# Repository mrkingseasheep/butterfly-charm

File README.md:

# Butterfly Charm

This is a very simple butterfly charm which is basically a light up trinket that you can hopefully attach to your bag.
It features large vias for keychains.
The LEDs only turn on when it is dark outside, preserving battery power and becoming more eye-catching in the dark.
The circuit uses a photoresistor in tandem with a transistor to determine whether or not it is light outside.
When there is light, the photoresistor decreases in resistence, therefore lowering electron flow to the base gate of the transistor, preventing the 2 LEDs from getting enough current to significantly light up.
When there is no light, the resistence in the photoresistor increases, therefore more current flows through the base gate (around 0.05miliamps) allowing 5 miliamps to run the LEDs.
Red LEDs were used because they need the least current.

Slack username: Xinyang Wang

## BOM

| Item                | Qnt |
| ------------------- | --- |
| LEDs                | 2   |
| Battery holder 3034 | 1   |
| Photoresistor       | 1   |
| 220ohm resistors    | 2   |
| 100kOhm resistors   | 1   |
| NPN transistor      | 1   |
| PCB                 | 1   |

## Images

## Thoughts

This was my first time designing a board using Kicad so it's a bit rough around the edges.
Getting the bezier curves to work was especially annoying and it took several iterations to smooth out the lumps.
There's probably a way to make an SVG the (Edges.Cuts) layer instead of having to polyline/curve it out but I'm too lazy to find out how.
The electronics are really simple. It's just connecting togther a battery, a LED, a resistor and a button.
Not much to explain. In fact, the most challenging part was designing the butterfly shape in Krita and getting the pattern on the back to work.
Oh hopefully the comically large vias won't destroy the structural stability of the part because I actually plan on using this.
If I have any advice for other people, it's to not use Kicad with a tiling window manager. It made things really difficult.
Also I almost forgot to run the checker. I just realized that my button holes weren't actually connected to the copper trace beneath them.
Hopefully nothing else is broken...

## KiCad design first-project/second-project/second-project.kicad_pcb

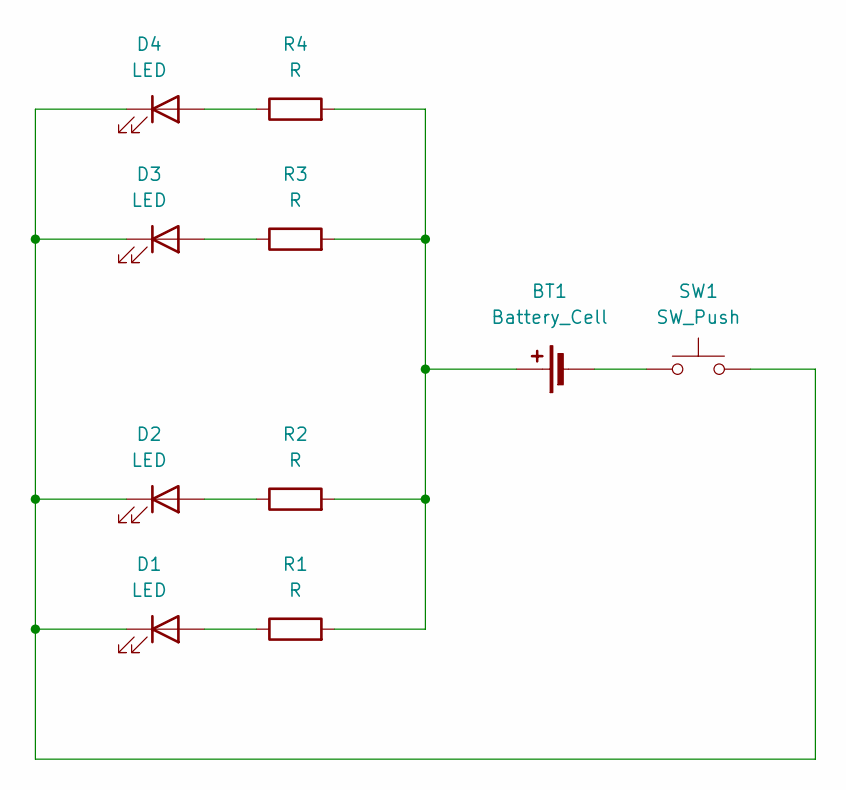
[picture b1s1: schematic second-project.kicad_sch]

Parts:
BT1: Battery_Cell; BatteryHolder_Keystone_3034_1x20mm
D1, D2, D3, D4: LED; LED_D5.0mm
R1, R2, R3, R4: R; R_Axial_DIN0207_L6.3mm_D2.5mm_P7.62mm_Horizontal
SW1: SW_Push; SW_PUSH_6mm

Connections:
unnamed: BT1.1 (+), R1.2, R2.2, R3.2, R4.2
unnamed: BT1.2 (-), SW1.1
unnamed: D1.2 (A), R1.1
unnamed: D1.1 (K), D2.1 (K), D3.1 (K), D4.1 (K), SW1.2
unnamed: D2.2 (A), R2.1
unnamed: D3.2 (A), R3.1
unnamed: D4.2 (A), R4.1

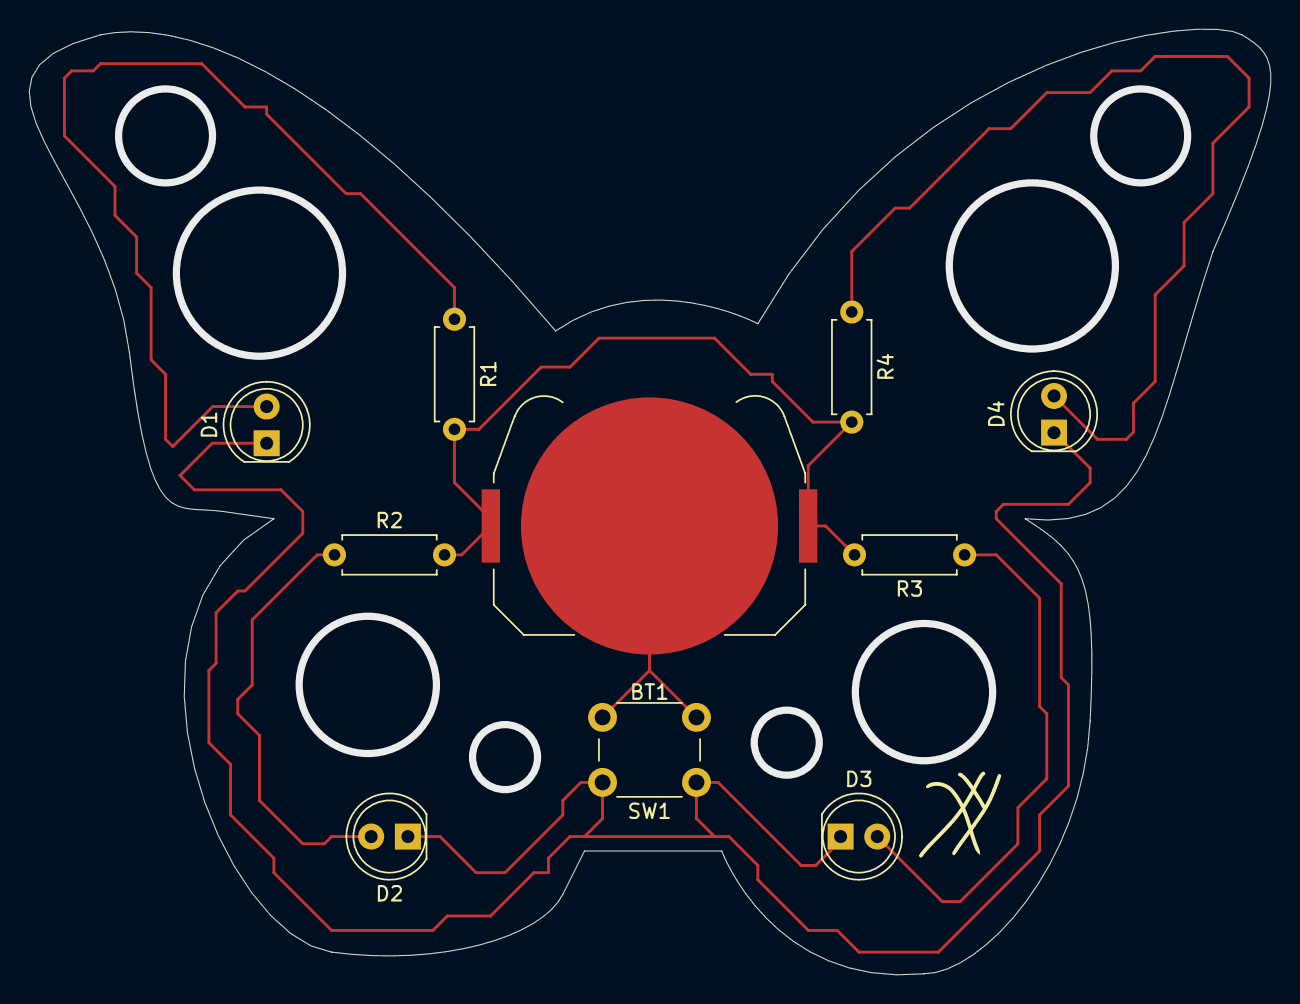
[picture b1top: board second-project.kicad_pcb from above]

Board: 2 copper layers, 85.9 x 65.5 mm, 10 parts (0 on the bottom side), 7 nets.

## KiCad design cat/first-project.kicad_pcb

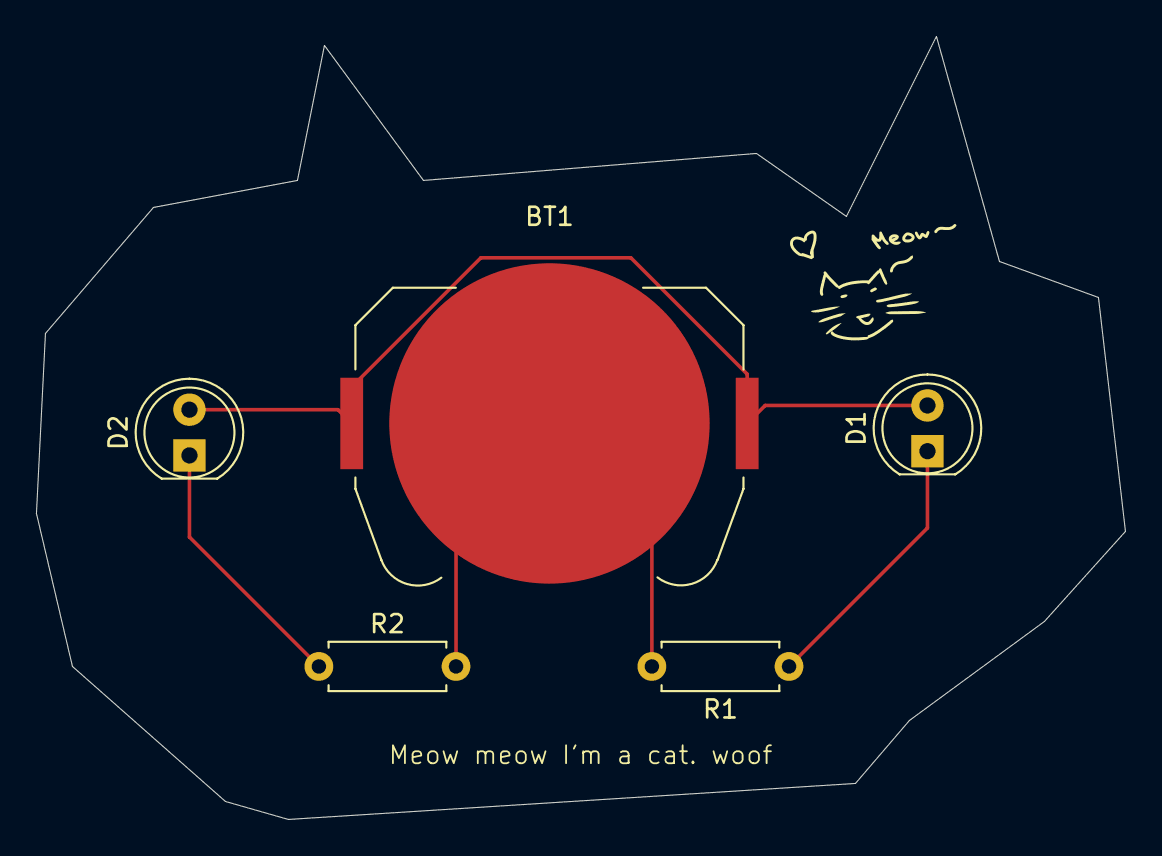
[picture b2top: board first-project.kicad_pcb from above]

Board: 2 copper layers, 60.5 x 43.5 mm, 5 parts (0 on the bottom side), 4 nets.

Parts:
BT1: Battery_Cell; BatteryHolder_Keystone_3034_1x20mm
D1, D2: LED; LED_D5.0mm
R1, R2: R; R_Axial_DIN0207_L6.3mm_D2.5mm_P7.62mm_Horizontal

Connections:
unnamed: BT1.1 (+), D1.2 (A), D2.2 (A)
unnamed: BT1.2 (-), R1.2, R2.2
unnamed: D1.1 (K), R1.1
unnamed: D2.1 (K), R2.1

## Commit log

2025-06-17 First cat
2025-06-18 second iteration
2025-06-18 added readme
2025-06-18 added images
2025-06-18 Fix images
2025-06-18 Fixed connection with button
2025-06-18 read me edit
2025-06-28 Responsive design finished
2025-06-28 more butterfly
